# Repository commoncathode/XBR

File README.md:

# XBR
The XBR is a cross-band repeater controller, intended for use with amateur radio transceivers. The radio ports are designed to work with the Yaesu FT-891 and Motorola XTL5000, but the circuitry is generic enough that, with some adjustment, it may very well work with a variety of radio transceivers. The heart of the controller is a Freescale/NXP 8-bit microcontroller, the MC9S08SH8.

**Background**

The main idea for this interface arose from the public service aspect of amateur (or "ham") radio. My club did a lot of public service events before the pandemic, such as foot and bike races. One event we were requested to assist with had a race course that covered much of the state, and so the differing terrain would make it difficult to maintain radio contact with the club's VHF repeater system. To fill in the weak spots, we thought "well, what about low band VHF, or even HF?" And I started to think, "better yet, what if all stations could hear one another, even if they were operating on a different band?" Thus, this interface is designed to link an HF/50 MHz radio to a VHF radio, in order to cross-link a VHF repeater onto an HF simplex frequency. Ideally, 28 or 50 MHz FM simplex linked to a 144 or 440 MHz repeater or repeater system.

**Operation**

Version 1 of the interface (or controller) is extremely simple in operation, designed to simply pass radio traffic automatically between two transcievers. It is not capable of linking repeaters or connecting to AllStar/Echolink. There is an impolite ID function that transmits on both radios every 10 minutes, non-adjustable. The tail is 500mS, non-adjustable. The ID function may be suitable for most users, but please follow your local governance for amateur radio operation. As I am in the US, the controller includes an active-low contact for disabling the repeater remotely to comply with FCC Part 97 regulations. There are many features I wish to add, but the intent was to develop a working, robust interface that provided reliable, legal operation of a cross-band repeater system at a base level.

**Revisions**

A few features I hope to add in the future are as follows.
- Capability to adjust all parameters over a serial terminal, such as:
- Call sign
- Tail length
- Polite ID function
- ID inactivity timer
- ID speed and pitch adjustment in words per minute (beta)
- Timeout timer length
- Enable/disable repeater over serial
- PTT and COR logic (active hi/lo)

**Errors**

1) With the components installed as outlined in the BoM, the ID function does not correctly pass audio to the mic inputs. You get sort of a "thumping" instead of a sine wave at 440Hz. This may be due to a low output impedance of the transformer coupled with the 10k resistors on the output; I am in the process of testing and verifying a few different solutions. 
2) The ID transformer's input is not referenced to common. I suggest scratching off some soldermask on the bottom next to the pad and bridging one side to the GND pour.
3) Impedance mismatch on the VHF port's mic circuit - just decoupled DC with a 4.7uF cap and jumped input to output in place of transformer TR2. This was an oddity with the radio I was using, so YMMV. 
Please view the schematic file or PDF print for a complete list of errata. 

Licensing is CC-BY-NC so please credit the author. Thanks!

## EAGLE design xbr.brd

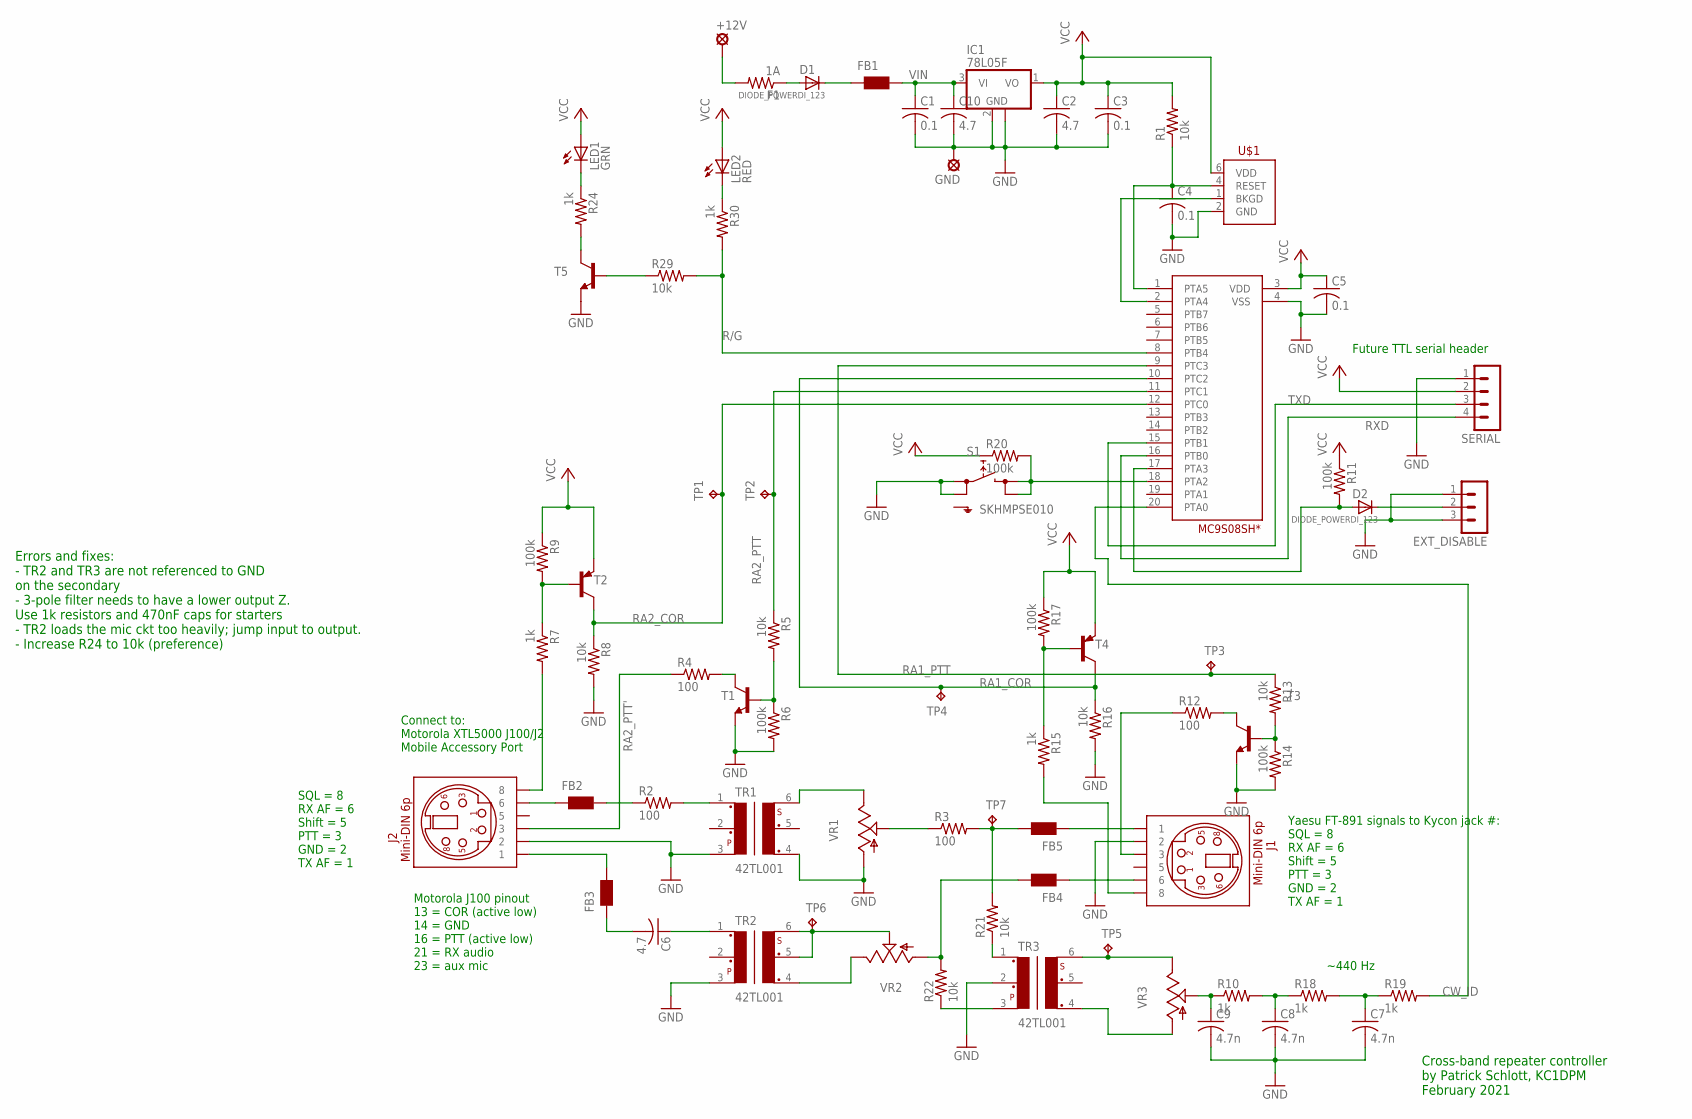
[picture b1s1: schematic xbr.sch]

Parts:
+12V: LSP10
C1, C3, C4, C5: 0.1; C0603
C2, C6, C10: 4.7; C0805
C7, C8, C9: 4.7n; C0603
D1, D2: DIODE_POWERDI_123; POWERDI_123
EXT_DISABLE: MA03-1
F1: 1A; R0603
FB1, FB2, FB3, FB4, FB5: WE-CBF_0805; 0805
GND: LSP10
IC1: 78L05F; SOT89
J1, J2: MINIDIN-6P; KMDTX-HT-6S-BSC
LED1: GRN; CHIPLED_0603
LED2: RED; CHIPLED_0805
R1, R5, R8, R13, R16, R21, R22, R29: 10k; R0603
R2, R3, R4, R12: 100; R1206
R6, R9, R11, R14, R17, R20: 100k; R0603
R7, R10, R15, R18, R19, R24, R30: 1k; R0603
S1: SKHMPSE010; SKHMPXE010
SERIAL: MA04-1
T1, T3, T5: MMBT2222ALT1-NPN-SOT23-BEC; SOT23-BEC
T2, T4: MMBT3906LT1-PNP-SOT23-BEC; SOT23-BEC
TP1, TP2, TP3, TP4, TP5, TP6, TP7: TPPAD1-13; P1-13
TR1, TR2, TR3: 42TL001; 42TL
U$1: BDM_HEADER; 2X03
U$2: MC9S08SH; PDIP-20
VR1, VR2, VR3: TRIM_US-B64Y; B64Y

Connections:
CW_ID: R19.2, U$2.20 (PTA0)
GND: C1.2, C2.2, C3.2, C4.2, C5.2, C7.2, C8.2, C9.2, C10.2, EXT_DISABLE.1, EXT_DISABLE.3, GND.MP, IC1.2 (GND), IC1.2@1 (GND), J1.2-GND (2), J2.2-GND (2), R6.2, R8.2, R14.2, R16.2, S1.1 (1.1), S1.2 (1.2), SERIAL.1, T1.E, T3.E, T5.E, TR1.3, TR1.4, TR2.3, TR3.2, U$1.2 (GND), U$2.4 (VSS), VR1.A
unnamed: C4.1, R1.1, U$1.4 (RESET), U$2.1 (PTA5)
unnamed: J2.8-SQL/COR (8), R7.2
unnamed: U$1.1 (BKGD), U$2.2 (PTA4)
unnamed: FB2.2, R2.1
unnamed: R2.2, TR1.1
unnamed: R7.1, R9.2, T2.B
unnamed: D1.K (C), FB1.1
unnamed: TR1.6, VR1.E
unnamed: R21.1, TR3.1
unnamed: R3.1, VR1.S
unnamed: FB5.2, R3.2, R21.2, TP7.TP
unnamed: TR2.4, VR2.E
unnamed: TP6.TP, TR2.5, TR2.6, VR2.S
unnamed: FB4.2, R22.2, VR2.A
unnamed: C6.1, TR2.1
unnamed: TP5.TP, TR3.6, VR3.E
unnamed: FB3.2, J2.1-DATA_IN (1)
unnamed: TR3.4, VR3.A
unnamed: R4.2, T1.C
unnamed: R5.2, R6.1, T1.B
unnamed: C9.1, R10.1, VR3.S
unnamed: D2.K (C), EXT_DISABLE.2
unnamed: D2.A, R11.2, U$2.17 (PTA3)
unnamed: R12.2, T3.C
unnamed: R13.2, R14.1, T3.B
unnamed: J1.8-SQL/COR (8), R15.2
unnamed: R15.1, R17.2, T4.B
unnamed: R20.2, S1.3 (2.1), S1.4 (2.2), U$2.18 (PTA2)
unnamed: R22.1, TR3.3
unnamed: C7.1, R18.2, R19.1
unnamed: C8.1, R10.2, R18.1
unnamed: LED1.C, R24.1
unnamed: R24.2, T5.C
unnamed: LED2.C, R30.1
unnamed: FB2.1, J2.6-DATA_OUT (6)
unnamed: R29.1, T5.B
unnamed: C6.2, FB3.1
unnamed: D1.A, F1.1
unnamed: +12V.MP, F1.2
unnamed: FB4.1, J1.6-DATA_OUT (6)
unnamed: FB5.1, J1.1-DATA_IN (1)
R/G: R29.2, R30.2, U$2.8 (PTB4)
RA1_COR: R16.1, T4.C, TP4.TP, U$2.10 (PTC2)
RA1_PTT: R13.1, TP3.TP, U$2.9 (PTC3)
RA1_PTT': J1.3-PTT (3), R12.1
RA2_COR: R8.1, T2.C, TP1.TP, U$2.12 (PTC0)
RA2_PTT: R5.1, TP2.TP, U$2.11 (PTC1)
RA2_PTT': J2.3-PTT (3), R4.1
RXD: SERIAL.4, U$2.16 (PTB0)
TXD: SERIAL.3, U$2.15 (PTB1)
VCC: C2.1, C3.1, C5.1, IC1.1 (VO), LED1.A, LED2.A, R1.2, R9.1, R11.1, R17.1, R20.1, SERIAL.2, T2.E, T4.E, U$1.6 (VDD), U$2.3 (VDD)
VIN: C1.1, C10.1, FB1.2, IC1.3 (VI)

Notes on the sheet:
Yaesu FT-891 signals to Kycon jack #: SQL = 8 RX AF = 6 Shift = 5 PTT = 3 GND = 2 TX AF = 1
Connect to: Motorola XTL5000 J100/J2 Mobile Accessory Port
Motorola J100 pinout 13 = COR (active low) 14 = GND 16 = PTT (active low) 21 = RX audio 23 = aux mic
SQL = 8 RX AF = 6 Shift = 5 PTT = 3 GND = 2 TX AF = 1
Future TTL serial header
Cross-band repeater controller by Patrick Schlott, KC1DPM February 2021
~440 Hz
Errors and fixes: - TR2 and TR3 are not referenced to GND on the secondary - 3-pole filter needs to have a lower output Z. Use 1k resistors and 470nF caps for starters - TR2 loads the mic ckt too heavily; jump input to output. - Increase R24 to 10k (preference)

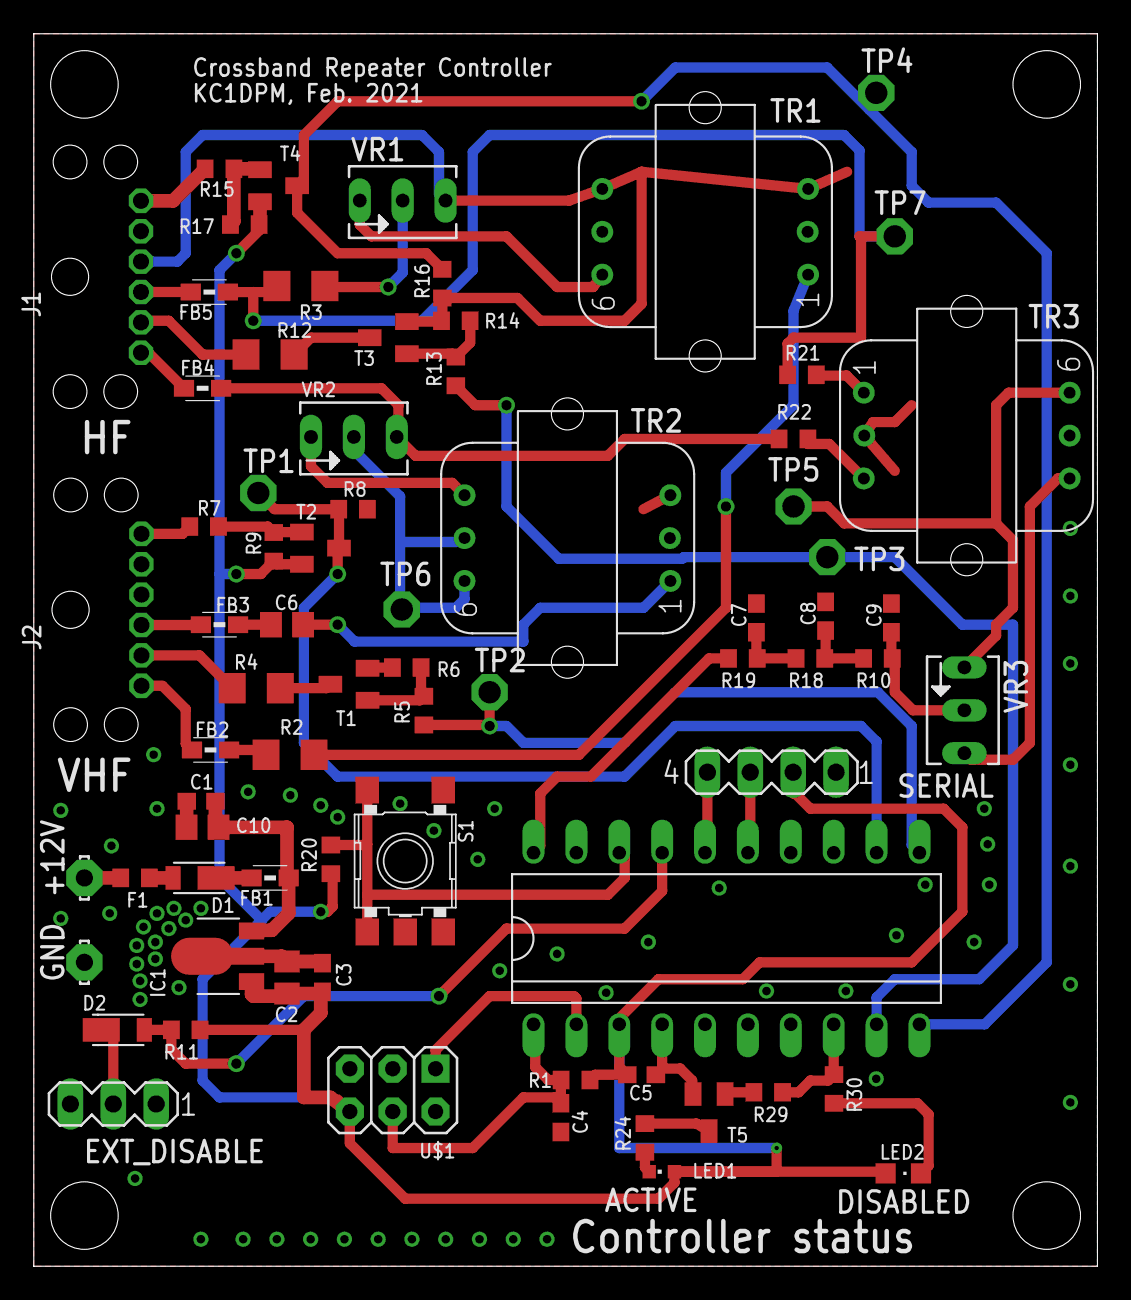
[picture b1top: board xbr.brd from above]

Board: 2 copper layers, 63.0 x 73.0 mm, 73 parts (0 on the bottom side), 54 nets.

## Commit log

2021-04-28 Adding pcb files, schematic and bom
    Important files for version 1 of the board. The PCB file has some errors, but the fixes and details are listed in the schematic.
    Firmware available upon request only.
2021-04-28 Formatting errors
2021-04-28 Added pictures
    Included populated circuit board plus custom project box with VHF receiver and DTMF relay board
2021-04-28 Added description of errors
2021-04-28 added stretch goal
2021-04-28 added more detail in "Operation"
2021-04-28 Added board pic
2021-04-28 Added creative commons licensing description.
